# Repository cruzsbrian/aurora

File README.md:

# Aurora
Aurora is an addressable LED controller with a graphical interface, audio input, and patterns programmed on an SD card.
It controls up to 8 WS2811-style LED strips in parallel.
A microphone and audio jack can be used for music visualization.
LED patterns are programmed in Lua and can be modified without rebooting by replacing the SD card.

[Interactive PCB BOM viewer](https://htmlpreview.github.io/?https://github.com/cruzsbrian/aurora/blob/main/aurora_hw/bom/ibom.html)

|  |  |
| ----------------------------- | ----------------------------------- |

## Configuring LED Strips

`aurora_sw/src/lights.h` contains configuration for the number of strips and their lengths and directions.

`N_STRIPS` is the total number of strips (starting from the top connector).  
`LEDS_PER_STRIP` the maximum number of LEDs on a single strip.  
`N_LEDS` is the total number of LEDs (the sum of all the strip lengths, less than or equal to `N_STRIPS * LEDS_PER_STRIP`).  
`n_leds[N_STRIPS]` is an array of the strip lengths.  
`led_dirs[N_STRIPS]` is an array of the strip directions.
1 indicates the strip should start from its first LED, -1 indicates it should start from its last LED.

## Writing Patterns

When an SD card is inserted, Aurora interprets each Lua file in its root directory as a pattern.
The title of a pattern is its filename, minus the `.lua` extension.

Every pattern must define an `update()` function to display one frame of its animation, which will be called at 50 Hz.

Patterns can set LED colors with the `setRGB(i, r, g, b)` and `setHSV(i, h, s, v)` functions, where `i` is the index of the LED (starting at 1 to follow the Lua convention) and the other parameters specify the color (all values ranging from 0 to 1).
Patterns can also inspect the current color of an LED with `getRGB(i)`, which returns the red, green, and blue values from 0 to 1.

Calling `print(arg1, arg2, ...)` from Lua prints to the serial console.

A pattern can specify any number of "parameters" for itself, which appear as sliders in the UI, with `add_param(name, min, max, step, default)`, where `name` is a string, and `max`, `min`, `step`, `default` are floating point numbers.
The parameter will then be available as a global variable in the Lua environment for that pattern (so `name` must be a valid Lua variable name).

Here is an example pattern which displays a rainbow repeated a configurable number of times (set by `cycles`) moving at a configurable speed:
```Lua
add_param("speed", 0, 1, 0.05, 0.15)
add_param("cycles", 1, 10, 1, 1)

start = 0

function update()
    for i=1,N_LEDS do
        -- Calculate hue based on LED position, rainbow start position, and number of cycles.
        h = ((i - start) * cycles / N_LEDS) % 1
        
        -- Set LED to calculated hue, full saturation, 25% brightness.
        setHSV(i, h, 1, 0.25)
    end

    start = start + speed
end
```

# Compile / Upload:
## Site Customization: : 
Although you can run the Aurora firmware as-is, you will probably want to go in and customize the LED settings to match the specific layout of your installation. This customization is done in the aurora_sw/src/lights.h file as follows. Examples are included for a few different possible configurations. 

Important Parameters:
- *LED_BRIGHTNESS:* How bright should "full" brightness be. Higher values will provide more light and color depth, but will also increase current use and may introduce color aberration on longer strips when many LEDs are lit. A default value of 100 will work in most environments. 
- *N_STRIPS:* How many different led strips there are. In this context a strip is defined as a group of LEDs which all share one signal line. 
- *LEDS_PER_STRIP:* The maximum number of LEDs on any one strip.
- *N_LEDS:* The total number of LEDs, this should be the sum of "n_leds".
- *n_leds:* How many LEDs there are in each strip. For custom installations it may be nessary to count, or to upload debug patterns to precisely determine this number. Incorrect values with result in lost pixels. 
- *led_dirs:* Which direction each strip runs relative to the direction of signal. You can pick either clockwise or counter-clockwise as the logic direction, but it must remain consistent to prevent animation jumps. Clockwise is a good default. 
## Windows Setup: 
Write-up Coming Soon!

## Linux Setup: 
The Linux install instructions assume that you have Version 1.x.x of the Arduino IDE installed, along with teensyduino which is used to upload code to the Teensy. Instructions for installing teensyduino (and links to arduino installers) can be found here: https://www.pjrc.com/teensy/teensyduino.html. It is definitely worth checking that your install works by uploading one of the teensy example scripts before proceeding. 

Setting up the build environment is pretty straightforward, but it does involve mucking around in the arduino libraries folder. If you have any questions definitely feel free to reach out. 

Using the arduino IDE Install: 
(Sketch -> Include Library -> Manage Libraries...)
 - SD
 - TFT_eSPI
 - lvgl
 - arduinoFFT (for debugging, optional)
 
 Navigate to your a libraries folder (likely /home/[name]/Arduino/libraries) and clone the [arduinoLua](https://github.com/blackketter/LuaArduino) repo. 
 
 Now copy the lv_conf.h file from /aurora_sw/src/ to the top level of your Arduino libraries folder. This configures the GUI generator.
 
 In your arduino libraries folder, replace TFT_eSPI/User_Setup.h with the User_Setup.h file provided in aurora_sw/src/. This configures the pins and dimensions of the display itself. 
 
 Rename /aurora_sw/src/main.cpp to /aurora_sw/src/main.ino so that it will be detected by the Arduino IDE. 
 
 You can now open src.ino with the Arduino IDE. 
 
 Before uploading you will need to set the optimizer (tools -> optimize) to "Smallest Code".
 
 You are now ready to upload!
 
 # Hardware Setup / Assembly: 
 
 ## Tips:
 - The MAX9814 is the board's most fiddly component, so if you are going to use the microphone, it pays to solder that first.
 - The fft_debug script can be used to check if the audio components are
   correctly installed. To use it install the script, and then play tones from
   your phone. The tones played and the tones reported on the serial monitor 
   should match to within 1hz or so over 200hz - 4000hz.

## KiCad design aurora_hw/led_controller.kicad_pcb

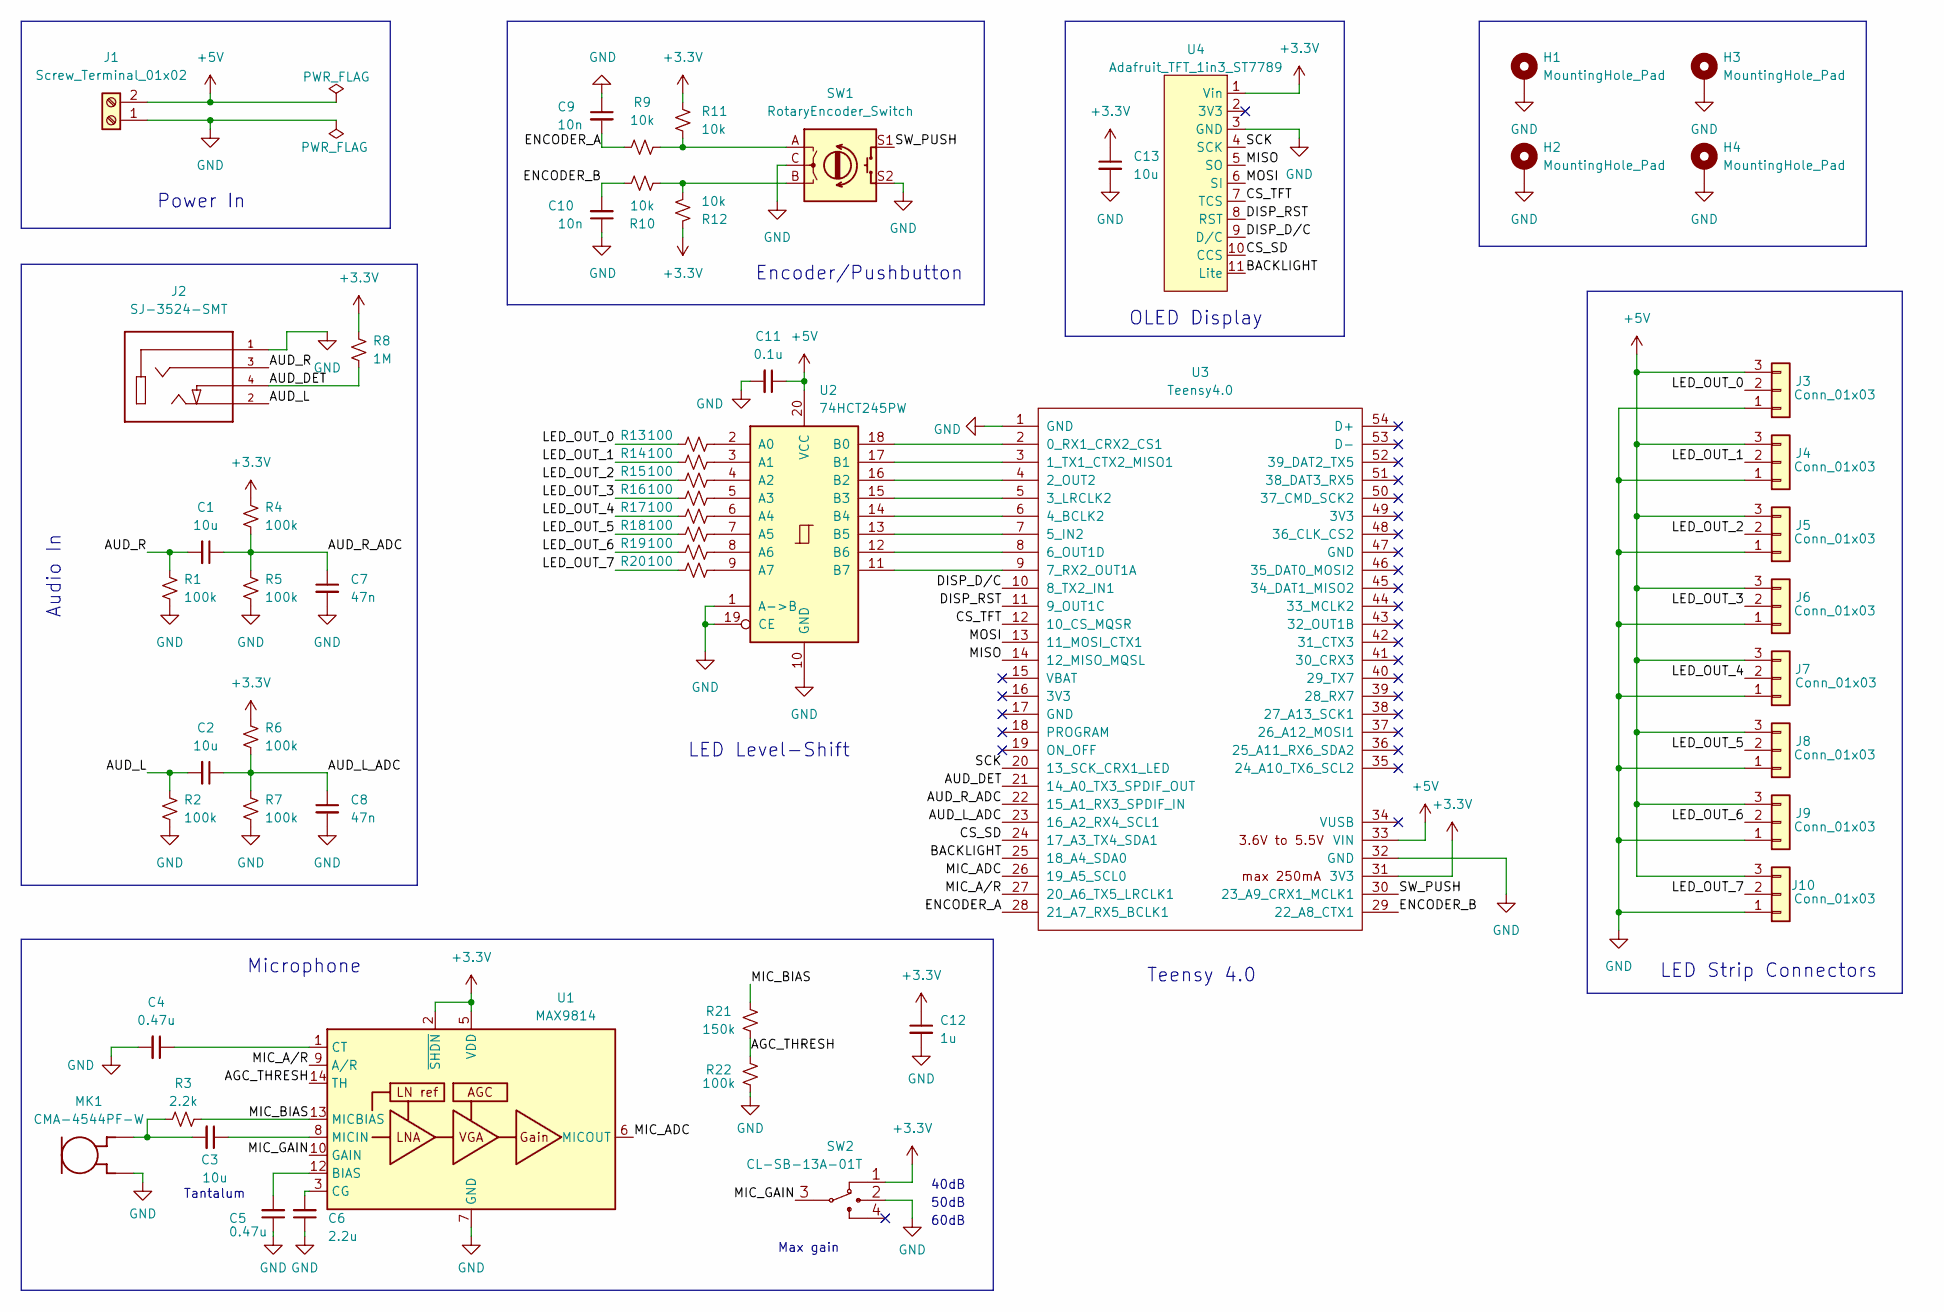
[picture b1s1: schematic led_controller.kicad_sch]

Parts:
C1, C2, C13: 10u; C_0805_2012Metric_Pad1.18x1.45mm_HandSolder
C3: 10u; C_0805_2012Metric_Pad1.18x1.45mm_HandSolder; LCSC Part Number C49678
C4, C5: 0.47u; C_0805_2012Metric_Pad1.18x1.45mm_HandSolder; LCSC Part Number C13967
C6: 2.2u; C_0805_2012Metric_Pad1.18x1.45mm_HandSolder; LCSC Part Number C49217
C7, C8: 47n; C_0805_2012Metric_Pad1.18x1.45mm_HandSolder
C9, C10: 10n; C_0805_2012Metric_Pad1.18x1.45mm_HandSolder; LCSC Part Number C1710
C11: 0.1u; C_0805_2012Metric_Pad1.18x1.45mm_HandSolder; LCSC Part Number C49678
C12: 1u; C_0805_2012Metric_Pad1.18x1.45mm_HandSolder; LCSC Part Number C49217
H1, H2, H3, H4: MountingHole_Pad; MountingHole_3.2mm_M3_ISO14580_Pad; LCSC Part Number N/A
J1: Screw_Terminal_01x02; TerminalBlock_Molex_393570002_1x02_P3.50mm_Horizontal; LCSC Part Number N/A
J2: SJ-3524-SMT; CUI_SJ-3524-SMT; LCSC Part Number N/A
J3, J4, J5, J6, J7, J8, J9, J10: Conn_01x03; JST_PH_S3B-PH-K_1x03_P2.00mm_Horizontal; LCSC Part Number N/A
MK1: CMA-4544PF-W; MIC_CMA-4544PF-W; LCSC Part Number N/A
R1, R2, R4, R5, R6, R7, R22: 100k; R_0805_2012Metric_Pad1.20x1.40mm_HandSolder; LCSC Part Number C149504
R3: 2.2k; R_0805_2012Metric_Pad1.20x1.40mm_HandSolder; LCSC Part Number C17520
R8: 1M; R_0805_2012Metric_Pad1.20x1.40mm_HandSolder
R9, R10, R11, R12: 10k; R_0805_2012Metric_Pad1.20x1.40mm_HandSolder; LCSC Part Number C17414
R13, R14, R15, R16, R17, R18, R19, R20: 100; R_0805_2012Metric_Pad1.20x1.40mm_HandSolder; LCSC Part Number C17408
R21: 150k; R_0805_2012Metric_Pad1.20x1.40mm_HandSolder; LCSC Part Number C17470
SW1: RotaryEncoder_Switch; RotaryEncoder_Alps_EC11E-Switch_Vertical_H20mm; LCSC Part Number N/A
SW2: CL-SB-13A-01T
U1: MAX9814; TDFN-14-1EP_3x3mm_P0.4mm_EP1.78x2.35mm_ThermalVias; LCSC Part Number C41714
U2: 74HCT245PW; TSSOP-20_4.4x6.5mm_P0.65mm; LCSC Part Number C5980
U3: Teensy4.0; Teensy40; LCSC Part Number N/A
U4: Adafruit_TFT_1in3_ST7789; LCSC Part Number N/A

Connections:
+3V3: C12.1, C13.1, R4.1, R6.1, R8.1, R11.1, R12.1, SW2.1, U1.2 (~SHDN), U1.5 (VDD), U3.31 (3V3), U4.1 (Vin)
+5V: C11.1, J1.2, J3.3, J4.3, J5.3, J6.3, J7.3, J8.3, J9.3, J10.3, U2.20 (VCC), U3.33 (VIN)
/AGC_THRESH: R21.1, R22.2, U1.14 (TH)
/AUD_DET: J2.4, R8.2, U3.21 (14_A0_TX3_SPDIF_OUT)
/AUD_L: C2.2, J2.2, R2.1
/AUD_L_ADC: C2.1, C8.1, R6.2, R7.1, U3.23 (16_A2_RX4_SCL1)
/AUD_R: C1.2, J2.3, R1.1
/AUD_R_ADC: C1.1, C7.1, R4.2, R5.1, U3.22 (15_A1_RX3_SPDIF_IN)
/BACKLIGHT: U3.25 (18_A4_SDA0), U4.11 (Lite)
/CS_SD: U3.24 (17_A3_TX4_SDA1), U4.10 (CCS)
/CS_TFT: U3.12 (10_CS_MQSR), U4.7 (TCS)
/DISP_D/C: U3.10 (8_TX2_IN1), U4.9 (D/C)
/DISP_RST: U3.11 (9_OUT1C), U4.8 (RST)
/ENCODER_A: C9.2, R9.2, U3.28 (21_A7_RX5_BCLK1)
/ENCODER_B: C10.2, R10.1, U3.29 (22_A8_CTX1)
/LED_OUT_0: J3.2, R13.1
/LED_OUT_1: J4.2, R14.1
/LED_OUT_2: J5.2, R15.1
/LED_OUT_3: J6.2, R16.1
/LED_OUT_4: J7.2, R17.1
/LED_OUT_5: J8.2, R18.1
/LED_OUT_6: J9.2, R19.1
/LED_OUT_7: J10.2, R20.1
/MIC_ADC: U1.6 (MICOUT), U3.26 (19_A5_SCL0)
/MIC_A/R: U1.9 (A/R), U3.27 (20_A6_TX5_LRCLK1)
/MIC_BIAS: R3.2, R21.2, U1.13 (MICBIAS)
/MIC_GAIN: SW2.3, U1.10 (GAIN)
/MISO: U3.14 (12_MISO_MQSL), U4.5 (SO)
/MOSI: U3.13 (11_MOSI_CTX1), U4.6 (SI)
/SCK: U3.20 (13_SCK_CRX1_LED), U4.4 (SCK)
/SW_PUSH: SW1.S1, U3.30 (23_A9_CRX1_MCLK1)
GND: C4.2, C5.1, C6.1, C7.2, C8.2, C9.1, C10.1, C11.2, C12.2, C13.2, H1.1, H2.1, H3.1, H4.1, J1.1, J2.1, J3.1, J4.1, J5.1, J6.1, J7.1, J8.1, J9.1, J10.1, MK1.2, R1.2, R2.2, R5.2, R7.2, R22.1, SW1.C, SW1.S2, SW2.2, U1.4 (GND), U1.7 (GND), U1.11 (GND), U1.15 (GND), U2.1 (A->B), U2.10 (GND), U2.19 (CE), U3.1 (GND), U3.32 (GND), U4.3 (GND)
unnamed: C3.1, U1.8 (MICIN)
unnamed: C3.2, MK1.1, R3.1
unnamed: C4.1, U1.1 (CT)
unnamed: C5.2, U1.12 (BIAS)
unnamed: C6.2, U1.3 (CG)
unnamed: R10.2, R12.2, SW1.B
unnamed: R9.1, R11.2, SW1.A
unnamed: R13.2, U2.2 (A0)
unnamed: R14.2, U2.3 (A1)
unnamed: R15.2, U2.4 (A2)
unnamed: R16.2, U2.5 (A3)
unnamed: R17.2, U2.6 (A4)
unnamed: R18.2, U2.7 (A5)
unnamed: R19.2, U2.8 (A6)
unnamed: R20.2, U2.9 (A7)
unnamed: U2.11 (B7), U3.9 (7_RX2_OUT1A)
unnamed: U2.12 (B6), U3.8 (6_OUT1D)
unnamed: U2.13 (B5), U3.7 (5_IN2)
unnamed: U2.14 (B4), U3.6 (4_BCLK2)
unnamed: U2.15 (B3), U3.5 (3_LRCLK2)
unnamed: U2.16 (B2), U3.4 (2_OUT2)
unnamed: U2.17 (B1), U3.3 (1_TX1_CTX2_MISO1)
unnamed: U2.18 (B0), U3.2 (0_RX1_CRX2_CS1)

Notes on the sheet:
50dB
Power In
Teensy 4.0
Encoder/Pushbutton
Max gain
Tantalum
60dB
Microphone
Audio In
40dB
LED Level-Shift
LED Strip Connectors
OLED Display

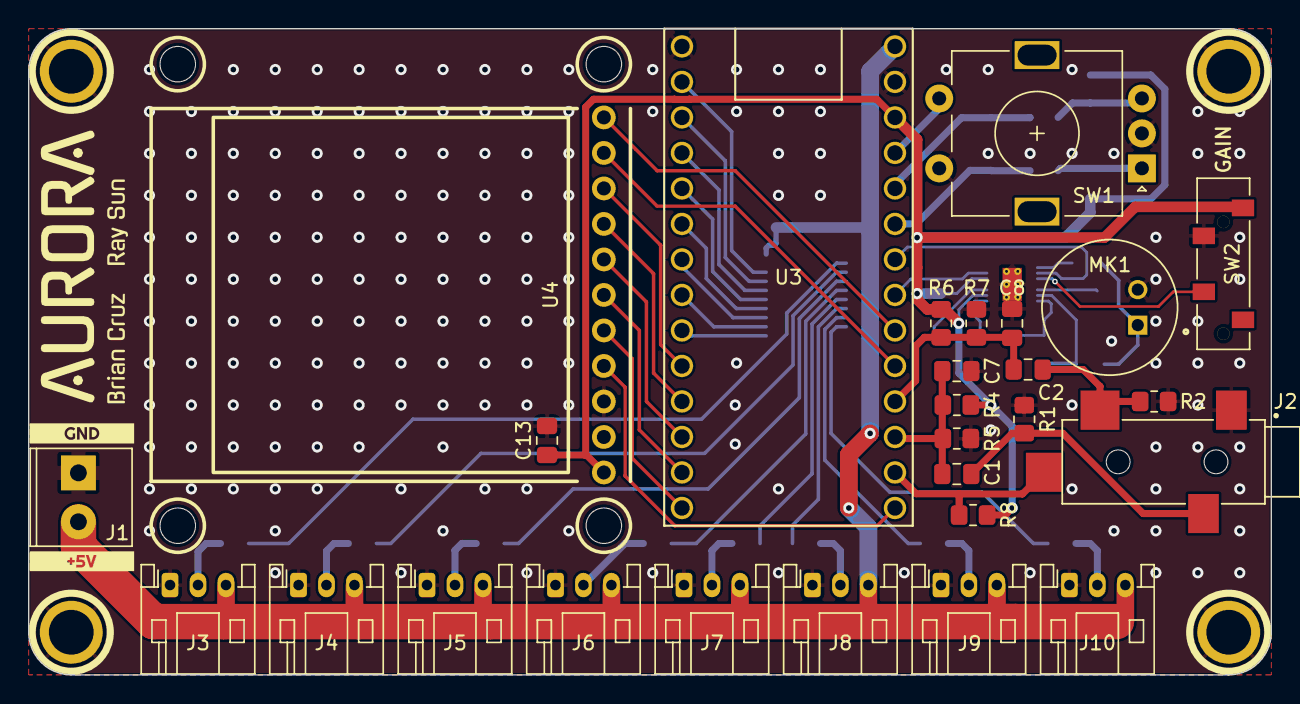
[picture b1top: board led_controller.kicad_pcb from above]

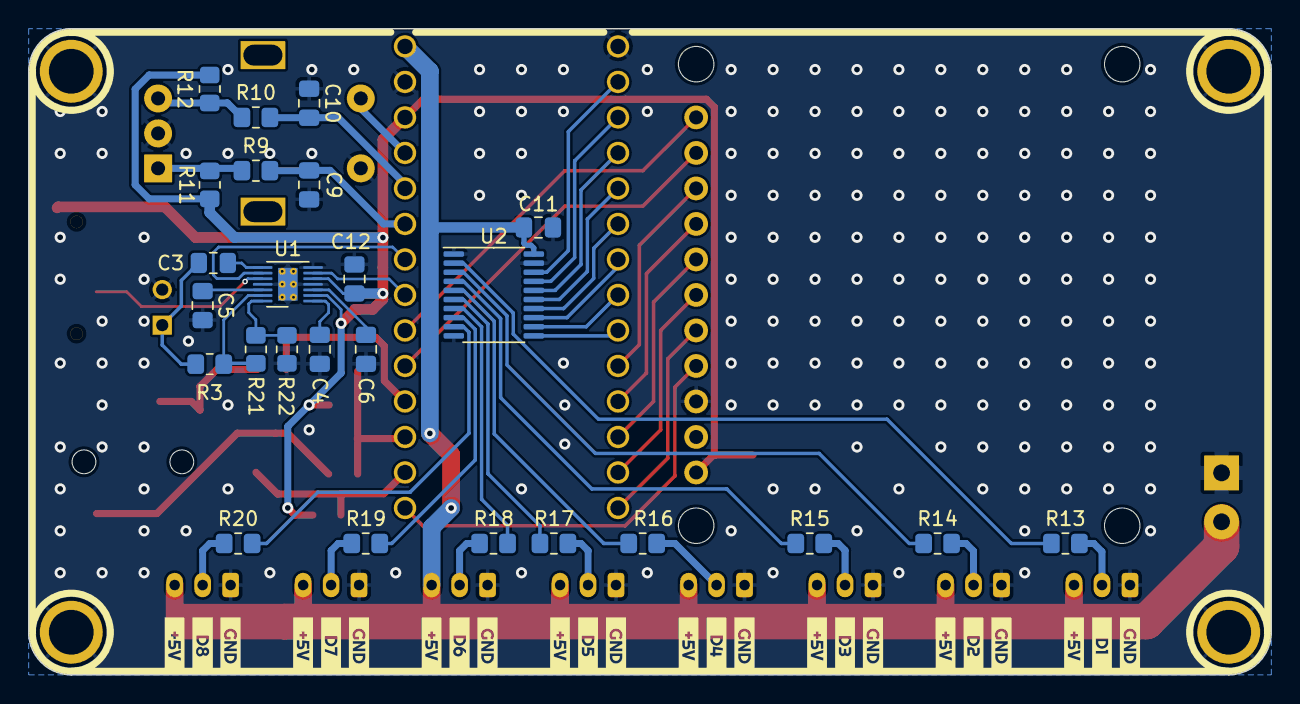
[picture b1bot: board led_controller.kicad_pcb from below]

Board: 2 copper layers, 88.9 x 46.2 mm, 84 parts (49 on the bottom side), 55 nets.

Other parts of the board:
kibuzzard-62AD5F1D: G***; kibuzzard-62AD5F1D
kibuzzard-62AD5F34: G***; kibuzzard-62AD5F34
kibuzzard-62AD6AEC, kibuzzard-62AD6AEC1, kibuzzard-62AD6AEC2, kibuzzard-62AD6AEC3, kibuzzard-62AD6AEC4, kibuzzard-62AD6AEC5, kibuzzard-62AD6AEC6, kibuzzard-62AD6AEC7: G***; kibuzzard-62AD6AEC
kibuzzard-62AD6B1, kibuzzard-62AD6B2, kibuzzard-62AD6B3, kibuzzard-62AD6B4, kibuzzard-62AD6B04, kibuzzard-62AD6B5, kibuzzard-62AD6B6, kibuzzard-62AD6B7: G***; kibuzzard-62AD6B04
kibuzzard-62AD6B13: G***; kibuzzard-62AD6B13
kibuzzard-62AD6BA8: G***; kibuzzard-62AD6BA8
kibuzzard-62AD6BC2: G***; kibuzzard-62AD6BC2
kibuzzard-62AD6C4C: G***; kibuzzard-62AD6C4C
kibuzzard-62AD6C16: G***; kibuzzard-62AD6C16
kibuzzard-62AD6C27: G***; kibuzzard-62AD6C27
kibuzzard-62AD6C38: G***; kibuzzard-62AD6C38
kibuzzard-62AD6C62: G***; kibuzzard-62AD6C62
kibuzzard-62AD66A7: G***; kibuzzard-62AD66A7
kibuzzard-62AD66B6: G***; kibuzzard-62AD66B6

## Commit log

2022-06-16 Start layout, choose display
2022-06-17 Place passives, route all except power
2022-06-18 Rearrange screen and power, add 3D models
2022-06-18 Finish routing, add text, via grid, round tracks
2022-06-18 Add origin markers, clean stackup, add some art
2022-06-18 Update Teensy model sockets
2022-06-19 Fix audio jack pinout and route jack insertion pin
2022-06-19 Enter pads at right angles for aesthetics
2022-06-20 Rearrange some analog pins, tweak routing
2022-06-20 Fix some clearance issues
2022-06-21 some more tweaks
2022-06-21 Update design rules
2022-06-21 Fix DRC clearance violations
2022-06-21 Generate position file
2022-06-22 Edit symbol fields for PCB assembly
2022-06-25 Switch to molex nano-fit connectors
2022-06-26 Revert "Switch to molex nano-fit connectors"
    This reverts commit 9b38a182e228fa806dde65dc415f981188c8a403.
2022-06-27 verified by Brian, create gerbers
2022-07-25 Clean up hw files, move to subfolder
2022-07-25 Set up vsteensy, start writing UI code
2022-08-28 Detecting SD card and loading pattern list
2022-08-28 Add lv_conf.h
2022-09-07 Basic pattern running with lua
2022-09-10 writing LEDs w/ OctoWS2811, HSV and print for lua
2022-09-12 User-defined parameters for patterns
2022-09-12 Make lights pin_list have all 8 pins
2022-09-12 Increase font size
2022-09-12 Use interrupts for patterns instead of Metro
2022-09-14 replace lua leds array with setRGB, setHSV, getRGB
2022-09-14 Replace interrupt with timer for pattern update
2022-09-14 Floating point params with mapping to min/max
2022-09-14 Add images
2022-09-14 Make linguist ignore the HTML BOM
2022-09-14 Add instructions for writing patterns
2022-09-20 Change BOM viewer link, add lib to linguist-vendored
2022-11-22 Add switch for changing A/R ratio, lengthen DFN pads
2022-11-22 Shrink mic amp GND pad to increase clearance
2023-01-05 Hardware v2
2023-01-05 Support different strip lengths, fix indexing
2023-01-05 Add pattern library
2023-01-05 Add PDF of schematic
2023-01-07 Fix strip config bug, move all config to lights.h
2023-01-07 Add config instructions to README
2023-01-07 Make getRGB scale the same as setRGB
2023-01-08 Add Fire2012 implementation, which is very slow for some reason.
2023-01-08 Fix speed. 4 quadrants are all the same.
2023-01-08 Fix nonuniform array slicing causing CR strip to not have orange
2023-01-08 Make 4-quadrant random version
2023-01-08 Make parameters consistent
2023-01-08 Allow uploading patterns over serial
2023-01-09 Blank LEDs when receiving pattern via serial
2023-01-09 Fix scrolling for menu subpages
2023-01-09 Send serial messages in one block
2023-02-05 Updated readme with install info
    Adds linux software setup directions, and some associated in-progress sections for hardware and windows.
2023-02-05 re-named src folder
2023-02-05 properly moved folder this time
2023-02-05 added user_Setup reference file
2023-02-05 exclude swap files from vim
2023-02-05 better solution for arduino IDE compatability.
2023-02-05 added audio debug script
2023-02-05 updated folder names
